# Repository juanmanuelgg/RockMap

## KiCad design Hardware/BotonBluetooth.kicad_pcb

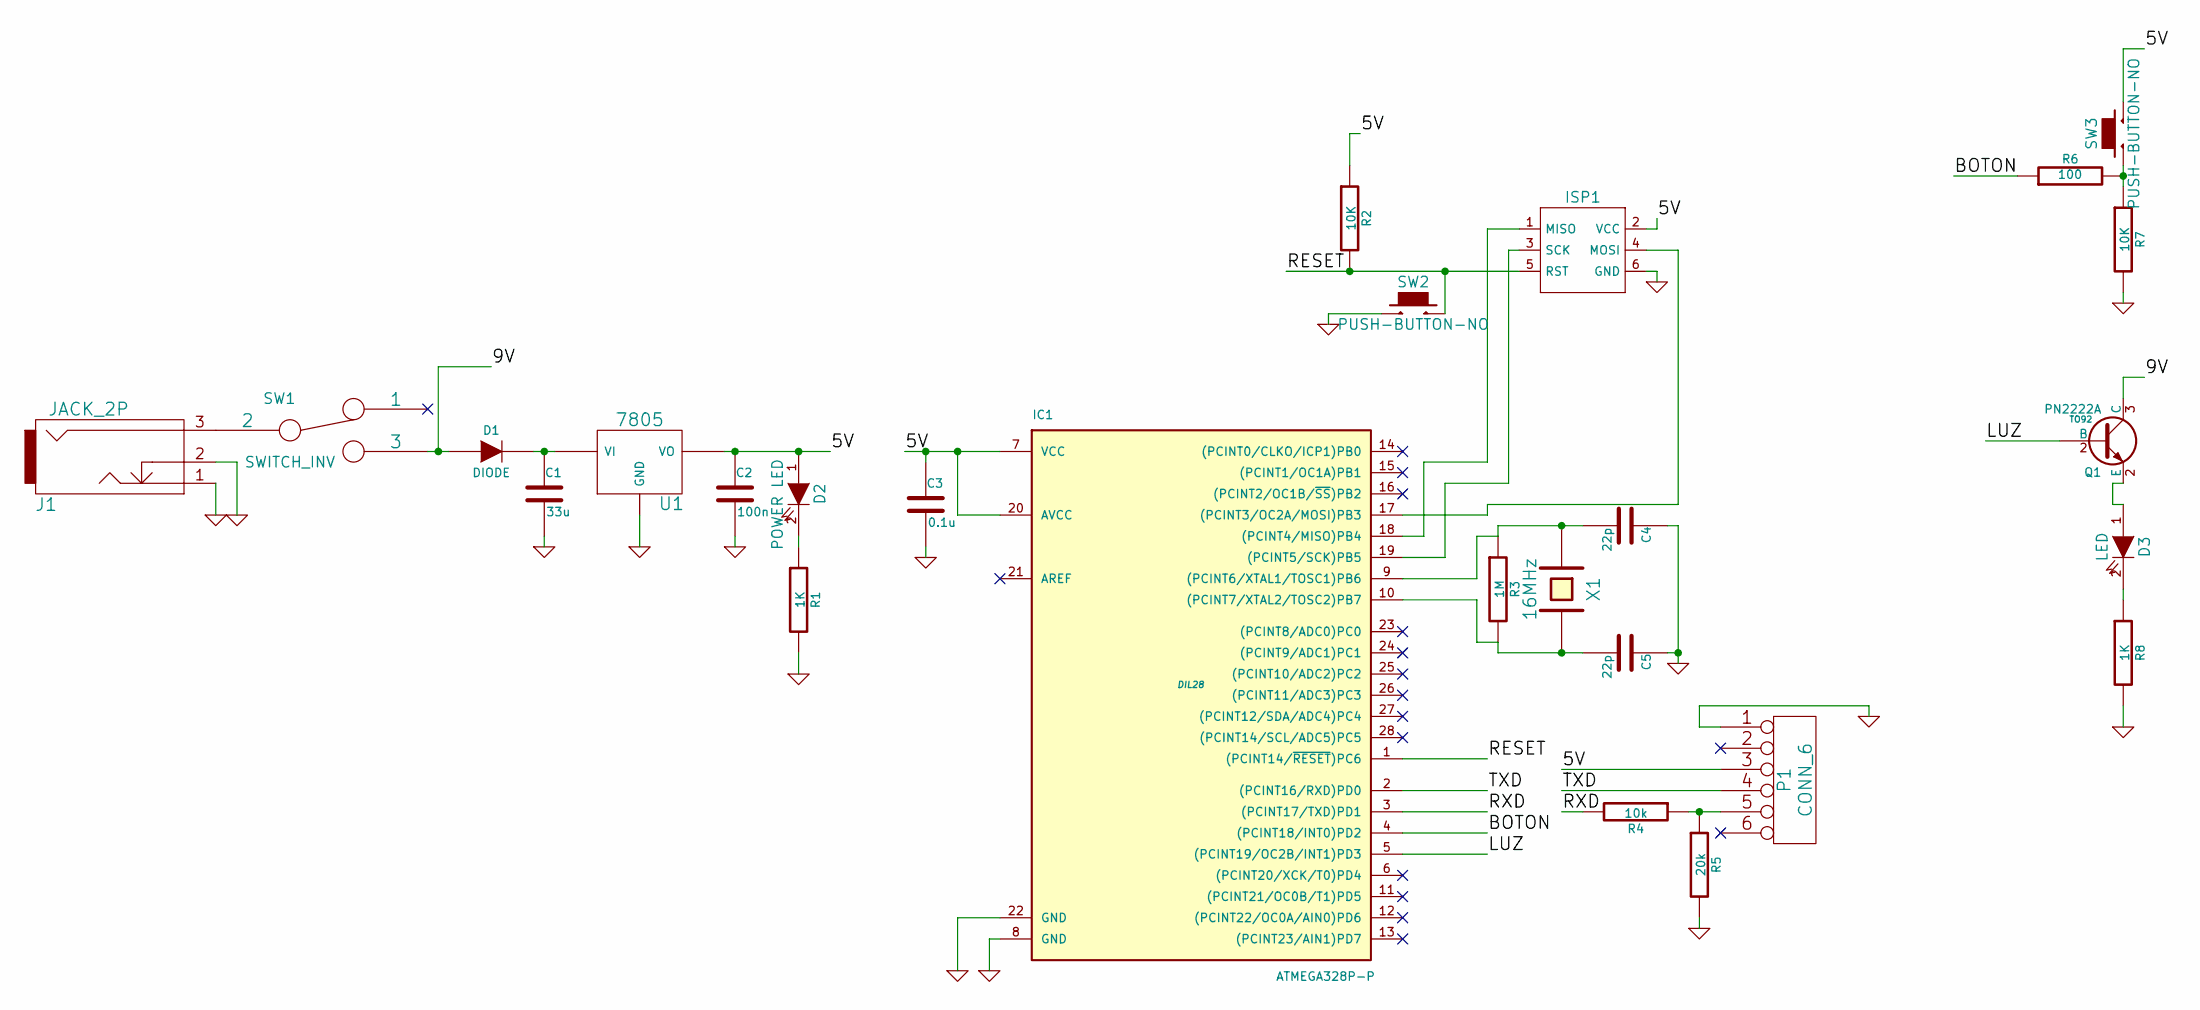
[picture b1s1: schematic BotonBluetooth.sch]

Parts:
C1: 33u
C2: 100n
C3: 0.1u
C4, C5: 22p
D1: DIODE
D2: POWER LED
D3: LED
IC1: ATMEGA328P-P; DIL28
ISP1: AVR_PRG_6PIN
J1: JACK_2P
P1: CONN_6
Q1: PN2222A; TO92
R1, R8: 1K
R2, R7: 10K
R3: 1M
R4: 10k
R5: 20k
R6: 100
SW1: SWITCH_INV
SW2, SW3: PUSH-BUTTON-NO
U1: 7805
X1: 16MHz

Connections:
/5V: C2.1, C3.1, D2.1 (A), IC1.7 (VCC), IC1.20 (AVCC), ISP1.2 (VCC), P1.3, R2.1, SW3.2, U1.VO
/9V: D1.1 (A), Q1.3 (C), SW1.3
/BOTON: IC1.4 ((PCINT18/INT0)PD2), R6.1
/RESET: IC1.1 ((PCINT14/~RESET~)PC6), ISP1.5 (RST), R2.2, SW2.2
/RXD: IC1.3 ((PCINT17/TXD)PD1), R4.2
/TXD: IC1.2 ((PCINT16/RXD)PD0), P1.4
GND: C1.2, C2.2, C3.2, C4.1, C5.1, IC1.8 (GND), IC1.22 (GND), ISP1.6 (GND), J1.1, J1.2, P1.1, R1.2, R5.2, R7.2, R8.2, SW2.1, U1.GND
unnamed: IC1.17 ((PCINT3/OC2A/MOSI)PB3), ISP1.4 (MOSI)
unnamed: IC1.18 ((PCINT4/MISO)PB4), ISP1.1 (MISO)
unnamed: D3.2 (K), R8.1
unnamed: R6.2, R7.1, SW3.1
unnamed: IC1.19 ((PCINT5/SCK)PB5), ISP1.3 (SCK)
unnamed: D2.2 (K), R1.1
unnamed: J1.3, SW1.2
unnamed: C4.2, IC1.9 ((PCINT6/XTAL1/TOSC1)PB6), R3.1, X1.1
unnamed: C5.2, IC1.10 ((PCINT7/XTAL2/TOSC2)PB7), R3.2, X1.2
unnamed: C1.1, D1.2 (K), U1.VI
unnamed: P1.5, R4.1, R5.1

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
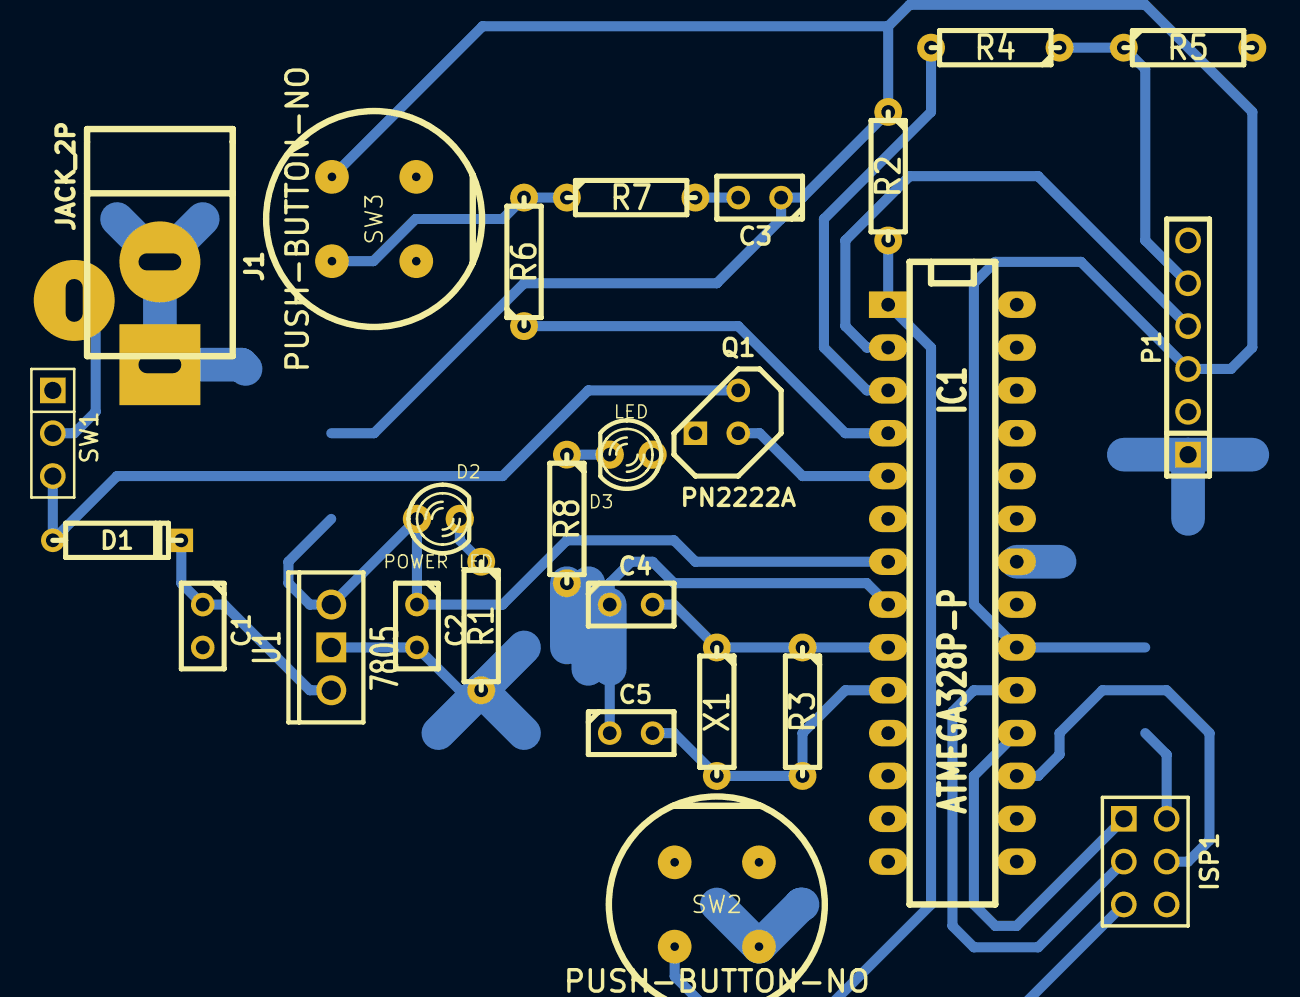
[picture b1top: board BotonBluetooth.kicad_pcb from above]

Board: 2 copper layers, 26 parts (0 on the bottom side), 19 nets.

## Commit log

2015-04-26 Componente de Hardware
2015-04-26 Hardware Bluetooth
2015-04-26 Proyecto SW
